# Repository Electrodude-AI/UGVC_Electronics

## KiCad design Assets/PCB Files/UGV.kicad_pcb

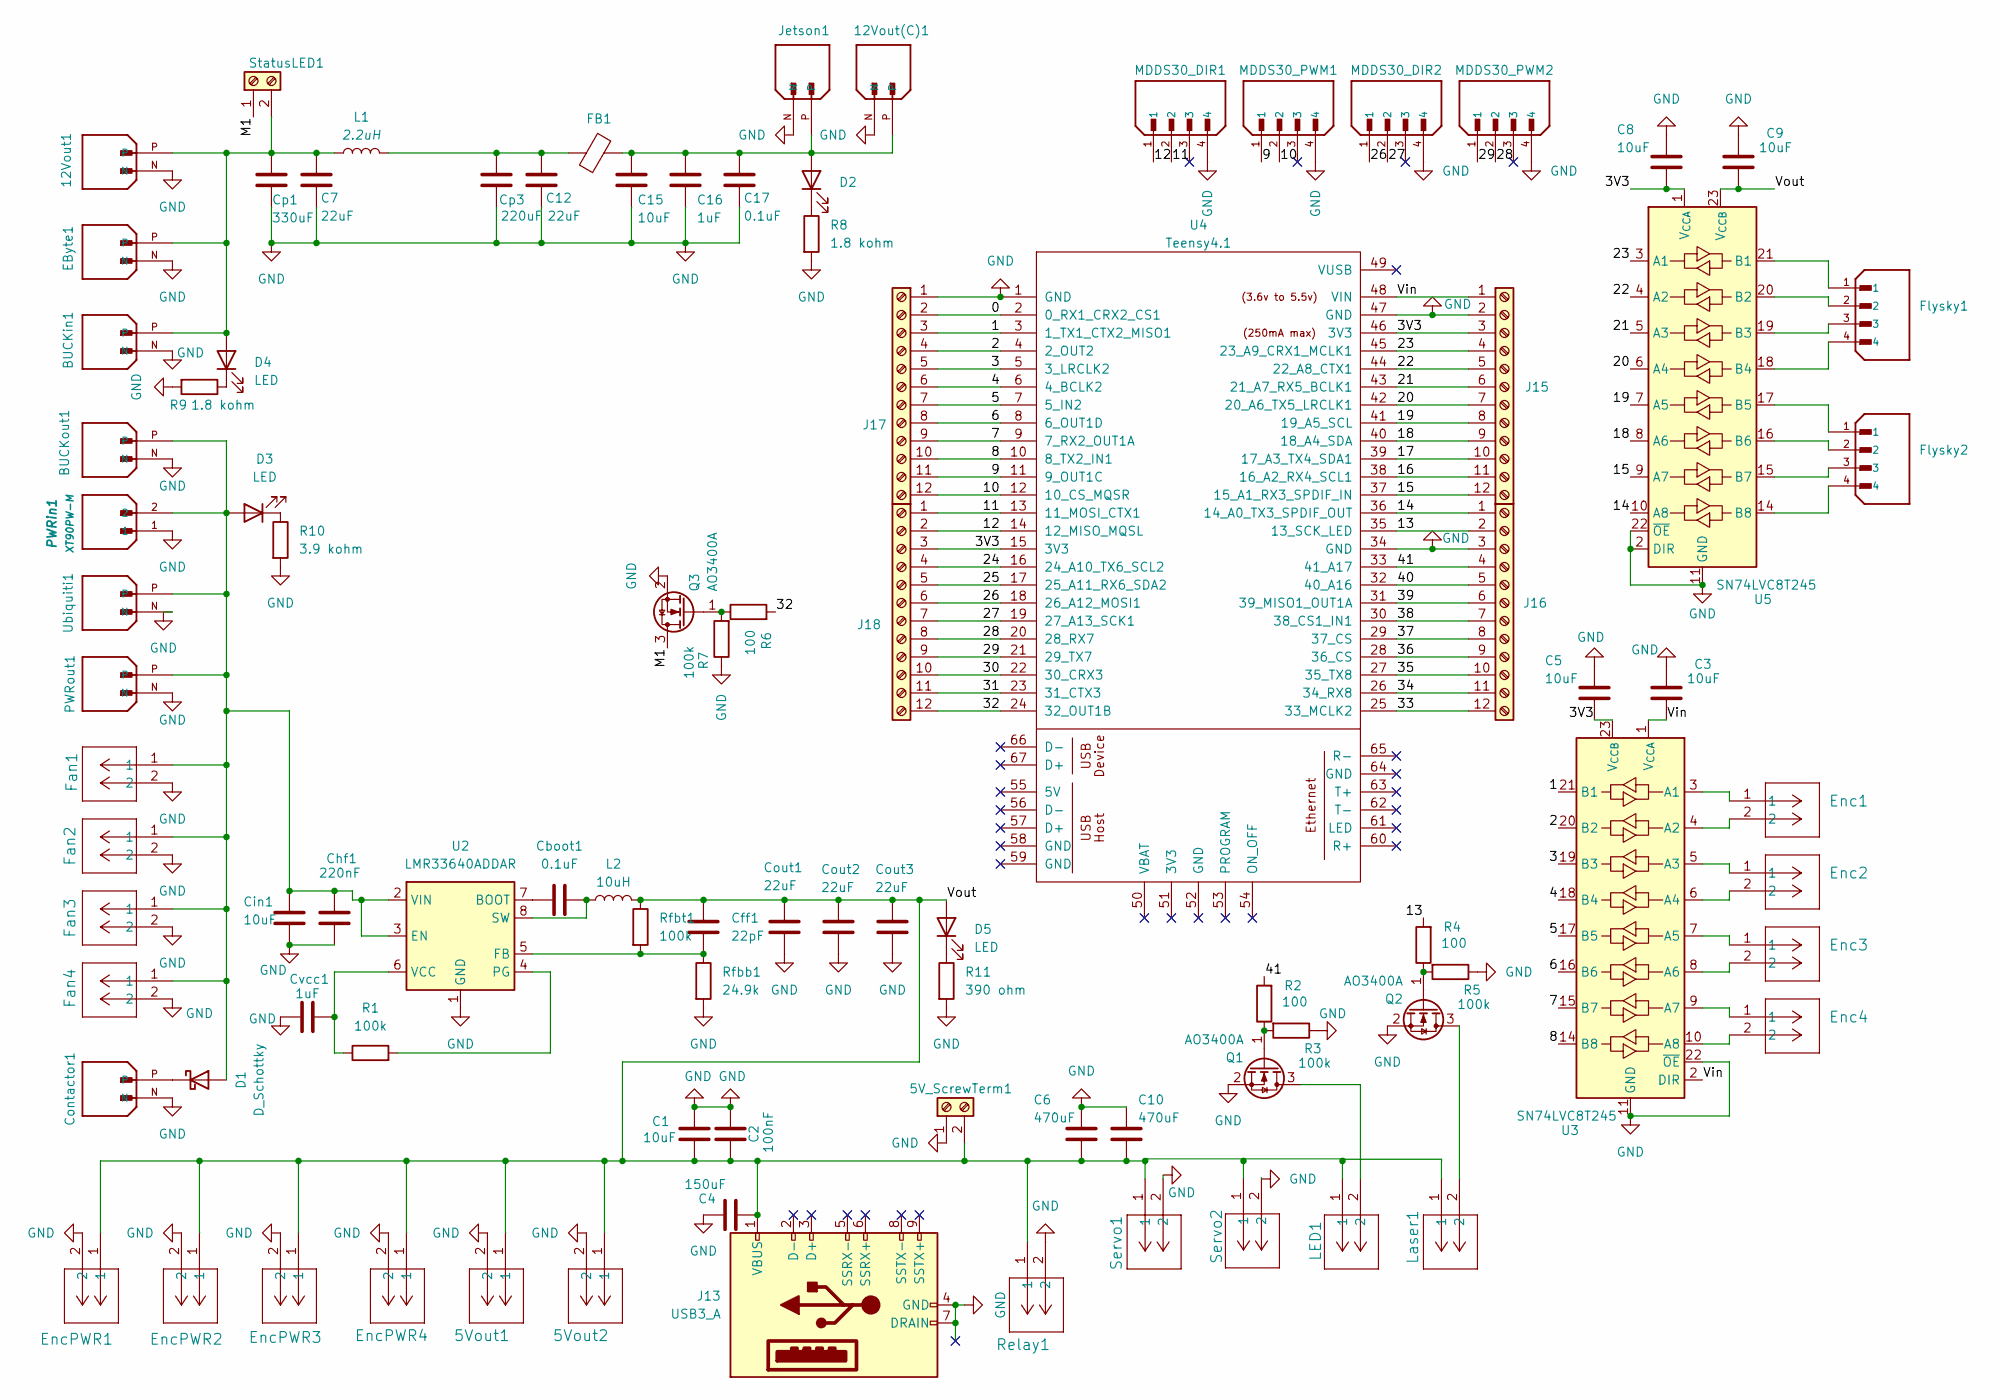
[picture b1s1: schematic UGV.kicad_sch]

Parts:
5V_ScrewTerm1: Screw_Terminal_01x02; TerminalBlock_Phoenix_MKDS-1,5-2-5.08_1x02_P5.08mm_Horizont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
5Vout1, 5Vout2: B2B-XH-A; JST_XH_B2B-XH-A_1x02_P2.50mm_Vertical
12Vout1, 12Vout(C)1: XT30PW-M; AMASS_XT30PW-M; PARTREV 1.2
BUCKin1: XT30PW-M; AMASS_XT30PW-M; PARTREV 1.2
BUCKout1: XT30PW-M; AMASS_XT30PW-M; PARTREV 1.2
C1, C3, C5, C8, C9, C15: 10uF; C_1210_3225Metric_Pad1.33x2.70mm_HandSolder
C2: 100nF; C_1206_3216Metric_Pad1.33x1.80mm_HandSolder
C4: 150uF; CP_Elec_8x10.5
C6, C10: 470uF; CP_Radial_D8.0mm_P3.50mm
C7, C12: 22uF; C_1210_3225Metric_Pad1.33x2.70mm_HandSolder
C16: 1uF; C_1206_3216Metric_Pad1.33x1.80mm_HandSolder
C17: 0.1uF; C_1206_3216Metric_Pad1.33x1.80mm_HandSolder
Cboot1: 0.1uF; C_1206_3216Metric_Pad1.33x1.80mm_HandSolder
Cff1: 22pF; C_0805_2012Metric_Pad1.18x1.45mm_HandSolder
Chf1: 220nF; C_1206_3216Metric_Pad1.33x1.80mm_HandSolder
Cin1: 10uF; C_1210_3225Metric_Pad1.33x2.70mm_HandSolder
Contactor1: XT30PW-M; AMASS_XT30PW-M; PARTREV 1.2
Cout1, Cout2, Cout3: 22uF; C_1210_3225Metric_Pad1.33x2.70mm_HandSolder
Cp1: 330uF; CP_Radial_D10.0mm_P5.00mm
Cp3: 220uF; CP_Elec_10x10
Cvcc1: 1uF; C_1206_3216Metric_Pad1.33x1.80mm_HandSolder
D1: D_Schottky; D_SMC_Handsoldering
D2, D3, D4, D5: LED; LED_1206_3216Metric_Pad1.42x1.75mm_HandSolder
EByte1: XT30PW-M; AMASS_XT30PW-M; PARTREV 1.2
Enc1, Enc2, Enc3, Enc4: B2B-XH-A-BK; JST_XH_B2B-XH-A_1x02_P2.50mm_Vertical
EncPWR1, EncPWR2, EncPWR3, EncPWR4: B2B-XH-A; JST_XH_B2B-XH-A_1x02_P2.50mm_Vertical
FB1: 1k@1k; L_0805_2012Metric_Pad1.05x1.20mm_HandSolder
Fan1, Fan2, Fan3, Fan4: B2B-XH-A-R; JST_XH_B2B-XH-A_1x02_P2.50mm_Vertical
Flysky1, Flysky2: B4B-XH-A_LF__SN_; JST_XH_B4B-XH-A_1x04_P2.50mm_Vertical; PARTREV 7/4/21
J13: USB3_A; USB-3.0-TH_U233-091N-4BLPC17-11
J15, J16, J17, J18: Screw_Terminal_01x12; TerminalBlock_Phoenix_MPT-0,5-12-2.54_1x12_P2.54mm_Horizont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
Jetson1: XT30PW-M; AMASS_XT30PW-M; PARTREV 1.2
L1: 2.2uH; L_Vishay_IHLP-2525
L2: 10uH; SRR1280-101M
LED1: B2B-XH-A; JST_XH_B2B-XH-A_1x02_P2.50mm_Vertical
Laser1: B2B-XH-A; JST_XH_B2B-XH-A_1x02_P2.50mm_Vertical
MDDS30_DIR1, MDDS30_DIR2, MDDS30_PWM1, MDDS30_PWM2: B4B-XH-A_LF__SN_; JST_XH_B4B-XH-A_1x04_P2.50mm_Vertical; PARTREV 7/4/21
PWRin1: XT90PW-M; AMASS_XT90PW-M_1x02_P10.90mm_Horizontal; PARTREV 1.2
PWRout1: XT30PW-M; AMASS_XT30PW-M; PARTREV 1.2
Q1, Q2, Q3: AO3400A; SOT-23_Handsoldering
R1, R3, R5, R7: 100k; R_1206_3216Metric_Pad1.30x1.75mm_HandSolder
R2, R4, R6: 100; R_0805_2012Metric_Pad1.20x1.40mm_HandSolder
R8, R9: 1.8 kohm; R_1206_3216Metric_Pad1.30x1.75mm_HandSolder
R10: 3.9 kohm; R_1206_3216Metric_Pad1.30x1.75mm_HandSolder
R11: 390 ohm; R_1206_3216Metric_Pad1.30x1.75mm_HandSolder
Relay1: B2B-XH-A; JST_XH_B2B-XH-A_1x02_P2.50mm_Vertical
Rfbb1: 24.9k; R_1206_3216Metric_Pad1.30x1.75mm_HandSolder
Rfbt1: 100k; R_1206_3216Metric_Pad1.30x1.75mm_HandSolder
Servo1, Servo2: B2B-XH-A; JST_XH_B2B-XH-A_1x02_P2.50mm_Vertical
StatusLED1: Screw_Terminal_01x02; TerminalBlock_Phoenix_MKDS-1,5-2-5.08_1x02_P5.08mm_Horizont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
U2: LMR33640ADDAR; LMR33630ADDAR; MPN LMR33630ADDAR
U3, U5: SN74LVC8T245; SOIC-24W_7.5x15.4mm_P1.27mm
U4: Teensy4.1; Teensy41
Ubiquiti1: XT30PW-M; AMASS_XT30PW-M; PARTREV 1.2

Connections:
/0: J17.2, U4.2 (0_RX1_CRX2_CS1)
/1: J17.3, U3.21 (B1), U4.3 (1_TX1_CTX2_MISO1)
/2: J17.4, U3.20 (B2), U4.4 (2_OUT2)
/3: J17.5, U3.19 (B3), U4.5 (3_LRCLK2)
/3V3: C5.2, C8.2, J15.3, J18.3, U3.23 (V_{CCB}), U3.24 (V_{CCB}), U4.15 (3V3), U4.46 (3V3), U5.1 (V_{CCA})
/4: J17.6, U3.18 (B4), U4.6 (4_BCLK2)
/5: J17.7, U3.17 (B5), U4.7 (5_IN2)
/6: J17.8, U3.16 (B6), U4.8 (6_OUT1D)
/7: J17.9, U3.15 (B7), U4.9 (7_RX2_OUT1A)
/8: J17.10, U3.14 (B8), U4.10 (8_TX2_IN1)
/9: J17.11, MDDS30_PWM1.1, U4.11 (9_OUT1C)
/10: J17.12, MDDS30_PWM1.2, U4.12 (10_CS_MQSR)
/11: J18.1, MDDS30_DIR1.2, U4.13 (11_MOSI_CTX1)
/12: J18.2, MDDS30_DIR1.1, U4.14 (12_MISO_MQSL)
/13: J16.2, R4.2, U4.35 (13_SCK_LED)
/14: J16.1, U4.36 (14_A0_TX3_SPDIF_OUT), U5.10 (A8)
/15: J15.12, U4.37 (15_A1_RX3_SPDIF_IN), U5.9 (A7)
/16: J15.11, U4.38 (16_A2_RX4_SCL1)
/17: J15.10, U4.39 (17_A3_TX4_SDA1)
/18: J15.9, U4.40 (18_A4_SDA), U5.8 (A6)
/19: J15.8, U4.41 (19_A5_SCL), U5.7 (A5)
/20: J15.7, U4.42 (20_A6_TX5_LRCLK1), U5.6 (A4)
/21: J15.6, U4.43 (21_A7_RX5_BCLK1), U5.5 (A3)
/22: J15.5, U4.44 (22_A8_CTX1), U5.4 (A2)
/23: J15.4, U4.45 (23_A9_CRX1_MCLK1), U5.3 (A1)
/24: J18.4, U4.16 (24_A10_TX6_SCL2)
/25: J18.5, U4.17 (25_A11_RX6_SDA2)
/26: J18.6, MDDS30_DIR2.1, U4.18 (26_A12_MOSI1)
/27: J18.7, MDDS30_DIR2.2, U4.19 (27_A13_SCK1)
/28: J18.8, MDDS30_PWM2.2, U4.20 (28_RX7)
/29: J18.9, MDDS30_PWM2.1, U4.21 (29_TX7)
/30: J18.10, U4.22 (30_CRX3)
/31: J18.11, U4.23 (31_CTX3)
/32: J18.12, R6.2, U4.24 (32_OUT1B)
/33: J16.12, U4.25 (33_MCLK2)
/34: J16.11, U4.26 (34_RX8)
/35: J16.10, U4.27 (35_TX8)
/36: J16.9, U4.28 (36_CS)
/37: J16.8, U4.29 (37_CS)
/38: J16.7, U4.30 (38_CS1_IN1)
/39: J16.6, U4.31 (39_MISO1_OUT1A)
/40: J16.5, U4.32 (40_A16)
/41: J16.4, R2.2, U4.33 (41_A17)
/M1: Q3.3 (D), StatusLED1.1
/Vin: C3.2, J15.1, U3.1 (V_{CCA}), U3.2 (DIR), U4.48 (VIN)
/Vout: 5V_ScrewTerm1.2, 5Vout1.1, 5Vout2.1, C1.2, C2.1, C4.1, C6.2, C9.2, C10.2, Cff1.1, Cout1.1, Cout2.1, Cout3.1, D5.2 (A), EncPWR1.1, EncPWR2.1, EncPWR3.1, EncPWR4.1, J13.1 (VBUS), L2.2, LED1.1, Laser1.1, Relay1.1, Rfbt1.1, Servo1.1, Servo2.1, U5.23 (V_{CCB}), U5.24 (V_{CCB})
GND: 5V_ScrewTerm1.1, 5Vout1.2, 5Vout2.2, 12Vout1.N, 12Vout(C)1.N, BUCKin1.N, BUCKout1.N, C1.1, C2.2, C3.1, C4.2, C5.1, C6.1, C7.2, C8.1, C9.1, C10.1, C12.2, C15.2, C16.2, C17.2, Chf1.2, Cin1.2, Contactor1.N, Cout1.2, Cout2.2, Cout3.2, Cp1.2, Cp3.2, Cvcc1.2, EByte1.N, EncPWR1.2, EncPWR2.2, EncPWR3.2, EncPWR4.2, Fan1.2, Fan2.2, Fan3.2, Fan4.2, J13.4 (GND), J13.7 (DRAIN), J15.2, J16.3, J17.1, Jetson1.N, MDDS30_DIR1.4, MDDS30_DIR2.4, MDDS30_PWM1.4, MDDS30_PWM2.4, PWRin1.1, PWRout1.N, Q1.2 (S), Q2.2 (S), Q3.2 (S), R3.1, R5.1, R7.1, R8.2, R9.2, R10.2, R11.2, Relay1.2, Rfbb1.2, Servo1.2, Servo2.2, U2.1 (GND), U2.9 (GND), U3.11 (GND), U3.12 (GND), U3.13 (GND), U3.22 (~OE), U4.1 (GND), U4.34 (GND), U4.47 (GND), U5.2 (DIR), U5.11 (GND), U5.12 (GND), U5.13 (GND), U5.22 (~OE), Ubiquiti1.N
unnamed: C12.1, Cp3.1, FB1.1, L1.2
unnamed: BUCKout1.P, Chf1.1, Cin1.1, D1.2 (A), D3.2 (A), Fan1.1, Fan2.1, Fan3.1, Fan4.1, PWRin1.2, PWRout1.P, U2.2 (VIN), U2.3 (EN), Ubiquiti1.P
unnamed: Contactor1.P, D1.1 (K)
unnamed: 12Vout(C)1.P, C15.1, C16.1, C17.1, D2.2 (A), FB1.2, Jetson1.P
unnamed: D2.1 (K), R8.1
unnamed: D3.1 (K), R10.1
unnamed: 12Vout1.P, BUCKin1.P, C7.1, Cp1.1, D4.2 (A), EByte1.P, L1.1, StatusLED1.2
unnamed: D4.1 (K), R9.1
unnamed: D5.1 (K), R11.1
unnamed: LED1.2, Q1.3 (D)
unnamed: Q1.1 (G), R2.1, R3.2
unnamed: Laser1.2, Q2.3 (D)
unnamed: Q2.1 (G), R4.1, R5.2
unnamed: Q3.1 (G), R6.1, R7.2
unnamed: Cboot1.1, U2.7 (BOOT)
unnamed: Cff1.2, Rfbb1.1, Rfbt1.2, U2.5 (FB)
unnamed: R1.2, U2.4 (PG)
unnamed: Cboot1.2, L2.1, U2.8 (SW)
unnamed: Cvcc1.1, R1.1, U2.6 (VCC)
unnamed: Enc1.1, U3.3 (A1)
unnamed: Enc1.2, U3.4 (A2)
unnamed: Enc2.1, U3.5 (A3)
unnamed: Enc2.2, U3.6 (A4)
unnamed: Enc3.1, U3.7 (A5)
unnamed: Enc3.2, U3.8 (A6)
unnamed: Enc4.1, U3.9 (A7)
unnamed: Enc4.2, U3.10 (A8)
unnamed: Flysky1.1, U5.21 (B1)
unnamed: Flysky1.2, U5.20 (B2)
unnamed: Flysky1.3, U5.19 (B3)
unnamed: Flysky1.4, U5.18 (B4)
unnamed: Flysky2.1, U5.17 (B5)
unnamed: Flysky2.2, U5.16 (B6)
unnamed: Flysky2.3, U5.15 (B7)
unnamed: Flysky2.4, U5.14 (B8)

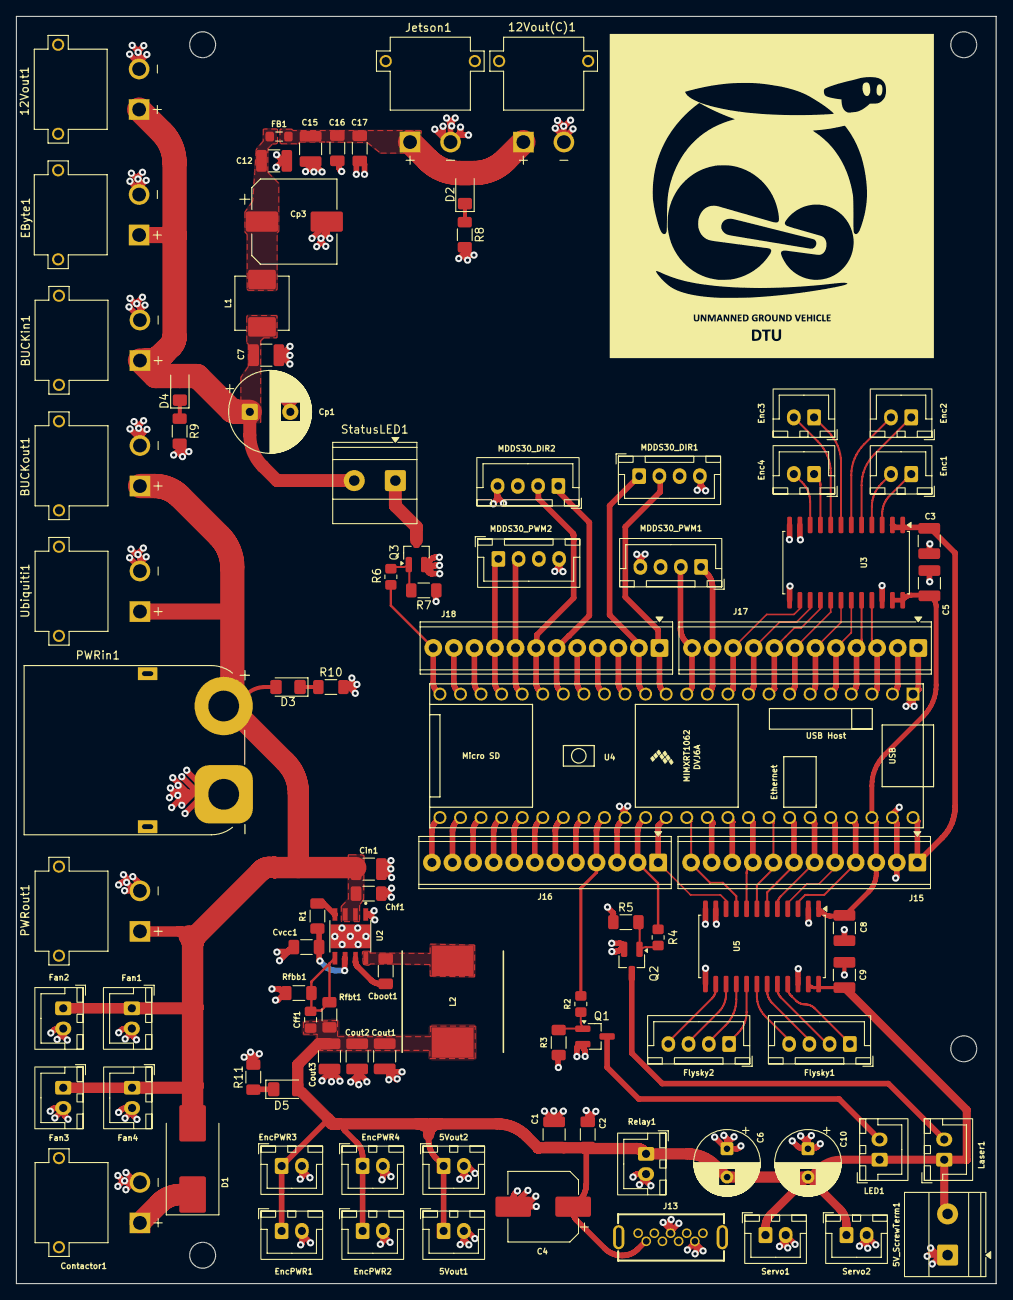
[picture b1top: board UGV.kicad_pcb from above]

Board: 2 copper layers, 121.0 x 156.5 mm, 94 parts (0 on the bottom side), 82 nets.

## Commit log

2026-05-05 PCB Done
2026-05-20 Changed the footprint
2026-05-22 Final PCB
2026-05-31 manual mode added
2026-05-31 Library updated
2026-06-04 Autonomous Mode
2026-06-05 initialized electronics repo
2026-06-06 safety mode
